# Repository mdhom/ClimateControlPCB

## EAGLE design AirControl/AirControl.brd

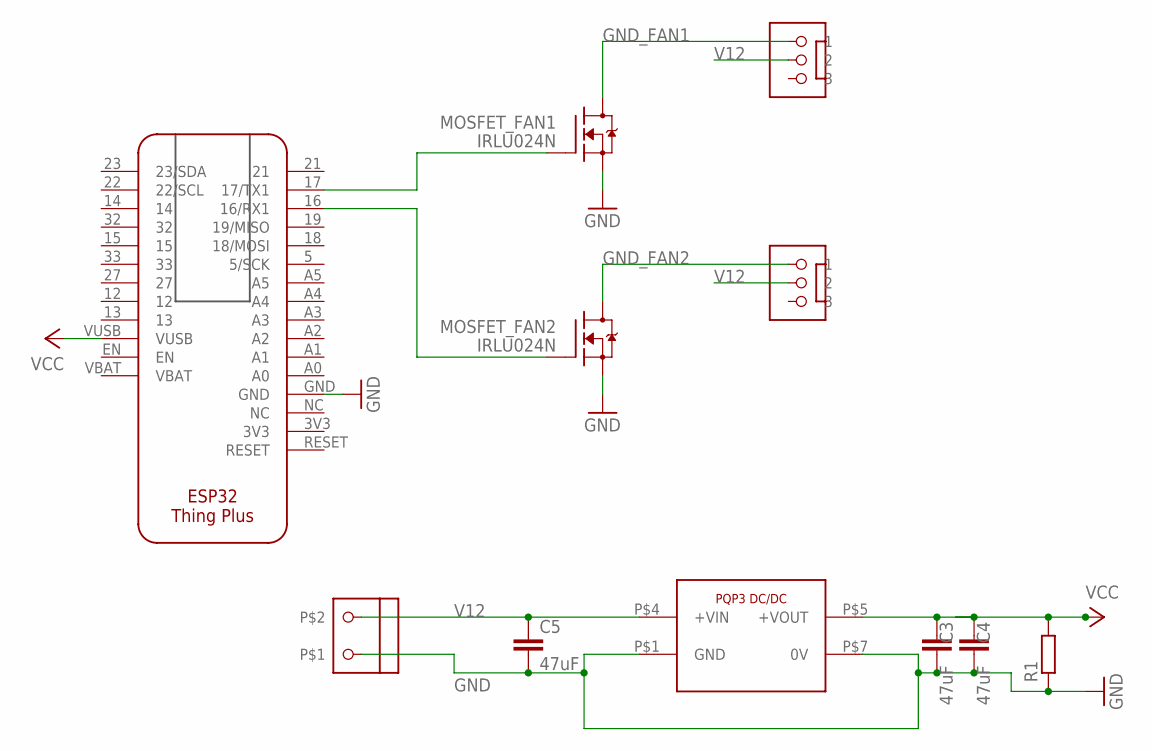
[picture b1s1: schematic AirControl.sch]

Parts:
C3, C4, C5: 47uF; C1210
MOSFET_FAN1, MOSFET_FAN2: IRLU024N; TO220-STANDING
PQP3: PQP3-D12-S5-DPQP3--D12-S5-D; PQP3-D
R1: R-EU_R1210; R1210
U$2: THING_PLUSTHING_PLUS; THING_PLUS
U$3, U$4: MOLEX_22-27-2031
U$5: AKL012-02

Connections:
GND: C3.2, C4.2, C5.2, MOSFET_FAN1.3 (S), MOSFET_FAN2.3 (S), PQP3.P$1 (GND), PQP3.P$7 (0V), R1.1, U$2.GND, U$5.P$1
GND_FAN1: MOSFET_FAN1.2 (D), U$3.P$1 (1)
GND_FAN2: MOSFET_FAN2.2 (D), U$4.P$1 (1)
unnamed: MOSFET_FAN1.1 (G), U$2.17 (17/TX1)
unnamed: MOSFET_FAN2.1 (G), U$2.16 (16/RX1)
V12: C5.1, PQP3.P$4 (+VIN), U$3.P$2 (2), U$4.P$2 (2), U$5.P$2
VCC: C3.1, C4.1, PQP3.P$5 (+VOUT), R1.2, U$2.VUSB

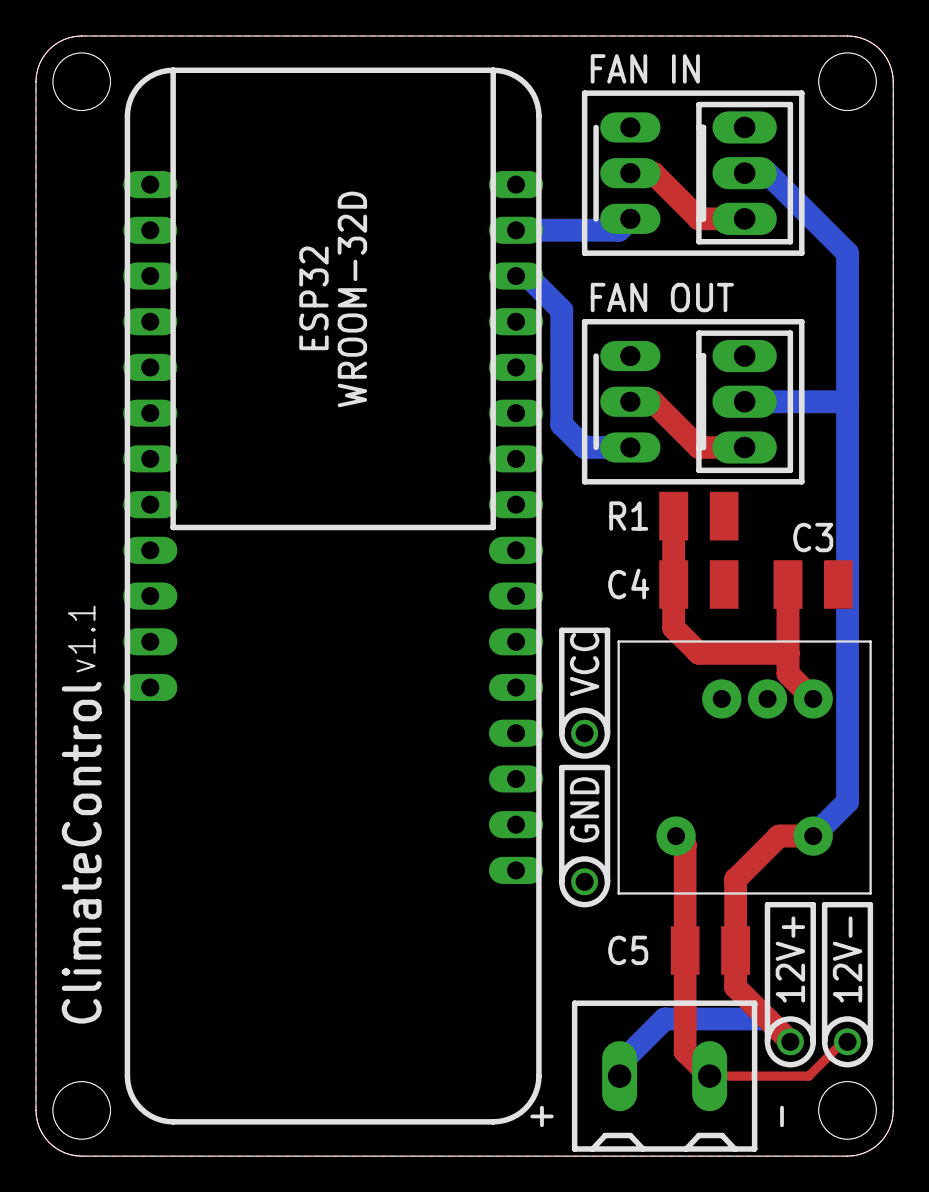
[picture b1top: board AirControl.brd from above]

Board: 2 copper layers, 47.6 x 62.2 mm, 11 parts (0 on the bottom side), 7 nets.
